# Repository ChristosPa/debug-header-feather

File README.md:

# debug-header-feather
Simple JTAG Debugging FeatherWing for the Adafruit Feather M0 development boards

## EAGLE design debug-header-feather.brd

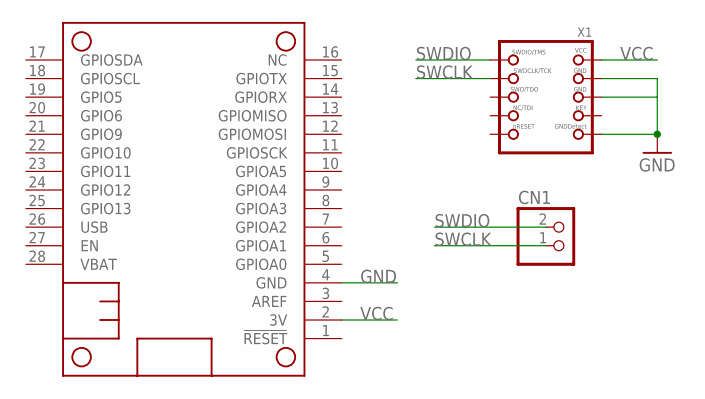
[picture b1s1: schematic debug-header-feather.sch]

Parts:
CN1: JST_2PIN-SMT-RA; JST-PH-2-SMT-RA
MS1: FEATHERWING
X1: JTAG-CORTEX; 2X05_1.27MM_SMT

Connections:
GND: MS1.4 (GND), X1.3 (GND), X1.5 (GND), X1.9 (GNDDETECT)
SWCLK: CN1.1 (2), X1.4 (SWDCLK)
SWDIO: CN1.2 (1), X1.2 (SWDIO)
VCC: MS1.2 (3V), X1.1 (VCC)

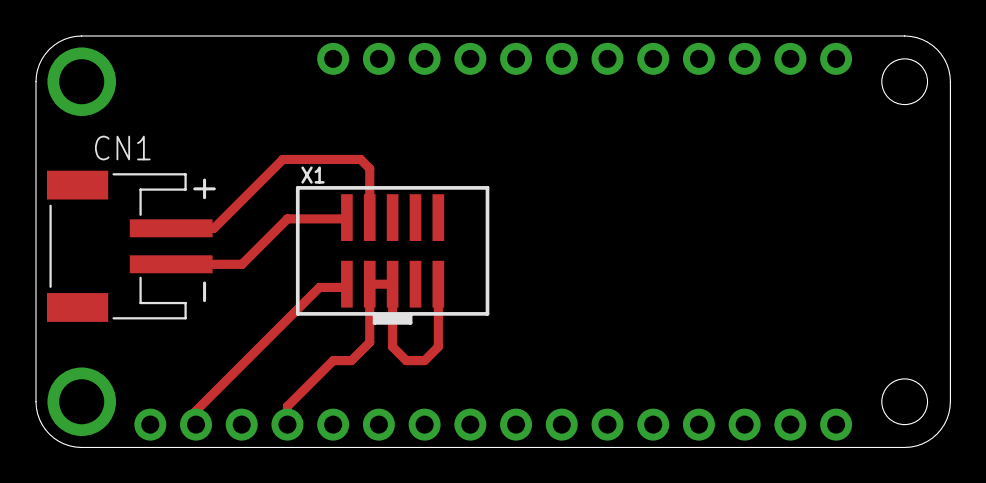
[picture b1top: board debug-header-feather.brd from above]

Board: 2 copper layers, 50.8 x 22.9 mm, 3 parts (0 on the bottom side), 4 nets.
